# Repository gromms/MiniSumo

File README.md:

# MiniSumo
Repository of mini sumo robot's electronics and programs of "Robotics Project" course.

# Team members
* Gromet Spaal
* Martin Maidla
* Simmo Saan

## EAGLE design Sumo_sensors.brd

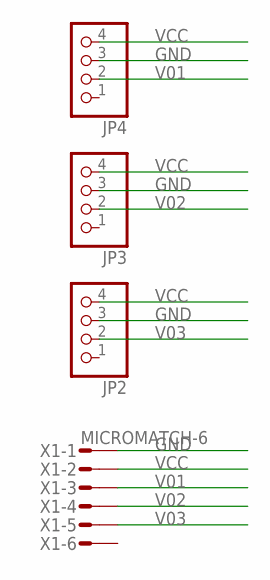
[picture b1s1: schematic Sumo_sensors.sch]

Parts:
JP2, JP3, JP4: PINHD-1X4; 1X04
X1: MICROMATCH-6

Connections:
GND: JP2.3, JP3.3, JP4.3, X1.1
V01: JP4.2, X1.3
V02: JP3.2, X1.4
V03: JP2.2, X1.5
VCC: JP2.4, JP3.4, JP4.4, X1.2

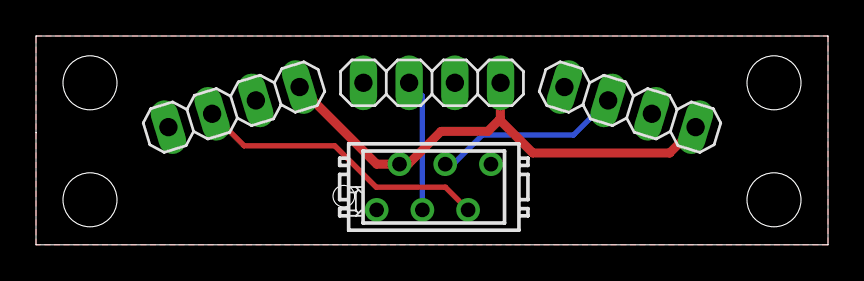
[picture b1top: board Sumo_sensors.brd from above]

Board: 2 copper layers, 44.0 x 11.6 mm, 4 parts (0 on the bottom side), 5 nets.

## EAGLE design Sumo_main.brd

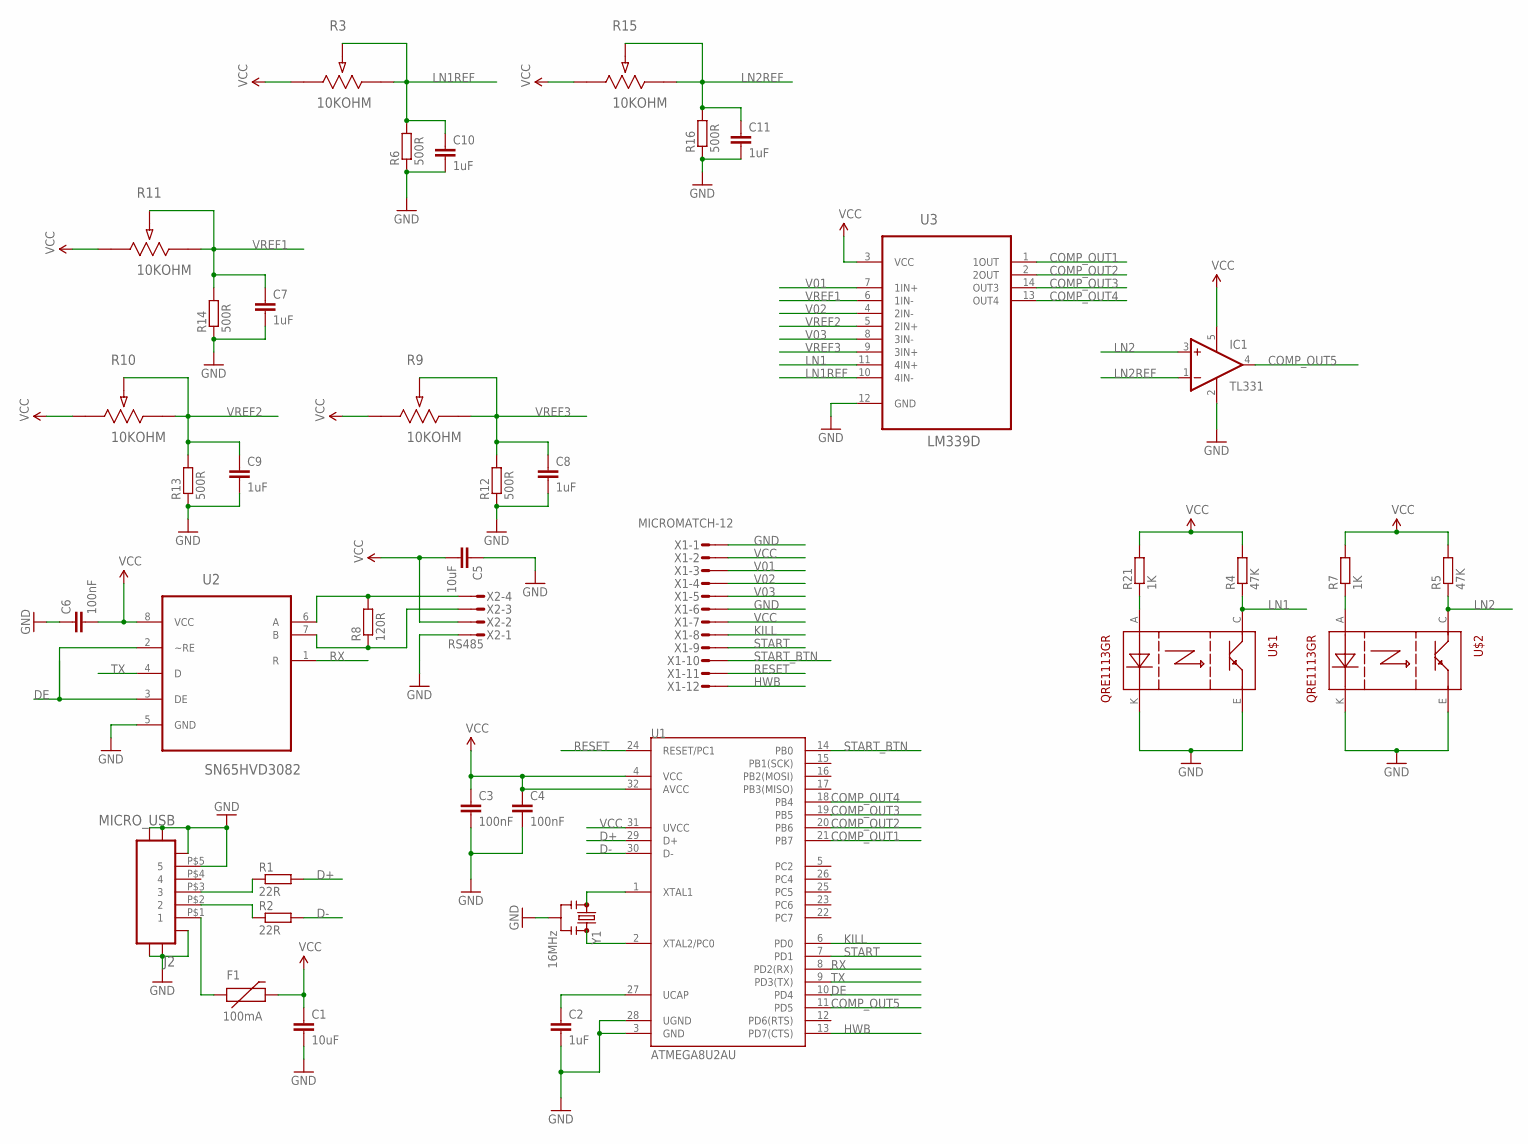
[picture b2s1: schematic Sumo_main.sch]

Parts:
C1, C5: 10uF; 0603-CAP
C2, C7, C8, C9, C10, C11: 1uF; 0603-CAP
C3, C4, C6: 100nF; 0603-CAP
F1: 100mA; PTC-1206
IC1: TL331; DBV-R-PDSO-G5
J2: MICRO_USB; MOLEX_47346-0001
R1, R2: 22R; R0603
R3, R9, R10, R11, R15: 10KOHM; POT_EVM3W
R4, R5: 47K; R0603
R6, R12, R13, R14, R16: 500R; R0603
R7, R21: 1K; R0603
R8: 120R; R0603
U1: ATMEGA8U2AU; TQFP32-08
U2: SN65HVD3082; SOIC127P600X175-8N
U3: LM339D; SOIC127P600X175-14N
U$1, U$2: QRE1113GR; 4LEADSMD
X1: MICROMATCH-12
X2: RS485; MICROMATCH-4
Y1: 16MHz; RESONATOR-SMD_MED

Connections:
COMP_OUT1: U1.21 (PB7), U3.1 (1OUT)
COMP_OUT2: U1.20 (PB6), U3.2 (2OUT)
COMP_OUT3: U1.19 (PB5), U3.14 (OUT3)
COMP_OUT4: U1.18 (PB4), U3.13 (OUT4)
COMP_OUT5: IC1.4 (OUT), U1.11 (PD5)
D+: R1.2, U1.29 (D+)
D-: R2.2, U1.30 (D-)
DE: U1.10 (PD4), U2.2 (~RE), U2.3 (DE)
GND: C1.2, C2.2, C3.2, C4.2, C5.1, C6.1, C7.2, C8.2, C9.2, C10.2, C11.2, IC1.2 (GND), J2.M1, J2.M2, J2.M3, J2.M4, J2.M5, J2.M6, J2.P$5 (5), R6.1, R12.1, R13.1, R14.1, R16.1, U1.3 (GND), U1.28 (UGND), U2.5 (GND), U3.12 (GND), U$1.E, U$1.K, U$2.E, U$2.K, X1.1, X1.6, X2.1, Y1.2
HWB: U1.13 (PD7(CTS)), X1.12
KILL: U1.6 (PD0), X1.8
LN1: R4.1, U3.11 (4IN+), U$1.C
LN1REF: C10.1, R3.2, R3.3, R6.2, U3.10 (4IN-)
LN2: IC1.3 (+IN), R5.1, U$2.C
LN2REF: C11.1, IC1.1 (-IN), R15.2, R15.3, R16.2
unnamed: J2.P$3 (3), R1.1
unnamed: J2.P$2 (2), R2.1
unnamed: F1.1, J2.P$1 (1)
unnamed: R21.1, U$1.A
unnamed: U1.1 (XTAL1), Y1.1
unnamed: U1.2 (XTAL2/PC0), Y1.3
unnamed: C2.1, U1.27 (UCAP)
unnamed: R7.1, U$2.A
unnamed: R8.2, U2.6 (A), X2.4
unnamed: R8.1, U2.7 (B), X2.3
RESET: U1.24 (RESET/PC1), X1.11
RX: U1.8 (PD2(RX)), U2.1 (R)
START: U1.7 (PD1), X1.9
START_BTN: U1.14 (PB0), X1.10
TX: U1.9 (PD3(TX)), U2.4 (D)
V01: U3.7 (1IN+), X1.3
V02: U3.4 (2IN-), X1.4
V03: U3.8 (3IN-), X1.5
VCC: C1.1, C3.1, C4.1, C5.2, C6.2, F1.2, IC1.5 (V+), R3.1, R4.2, R5.2, R7.2, R9.1, R10.1, R11.1, R15.1, R21.2, U1.4 (VCC), U1.31 (UVCC), U1.32 (AVCC), U2.8 (VCC), U3.3 (VCC), X1.2, X1.7, X2.2
VREF1: C7.1, R11.2, R11.3, R14.2, U3.6 (1IN-)
VREF2: C9.1, R10.2, R10.3, R13.2, U3.5 (2IN+)
VREF3: C8.1, R9.2, R9.3, R12.2, U3.9 (3IN+)

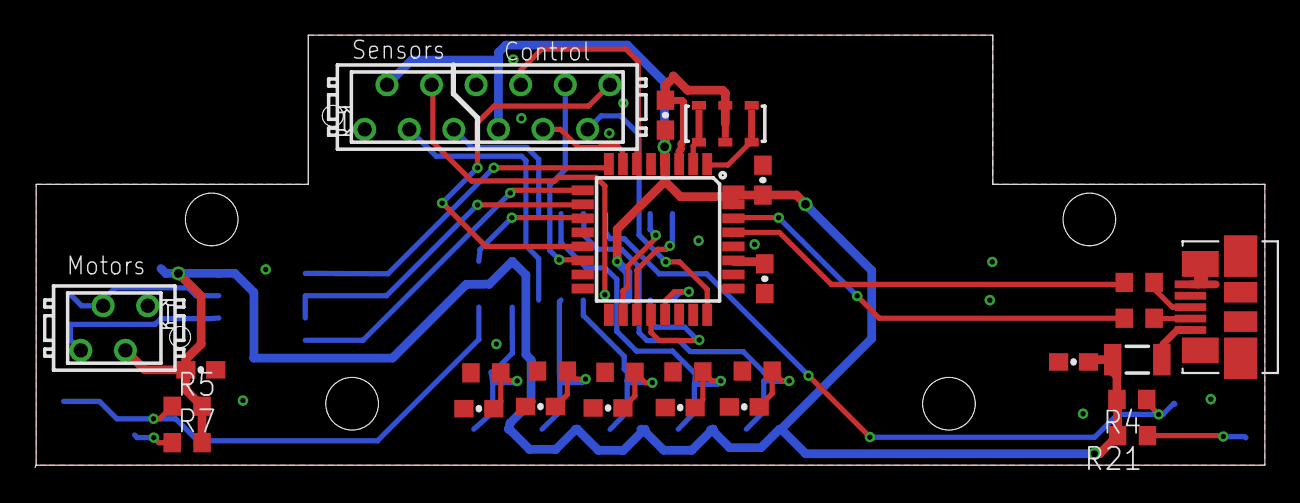
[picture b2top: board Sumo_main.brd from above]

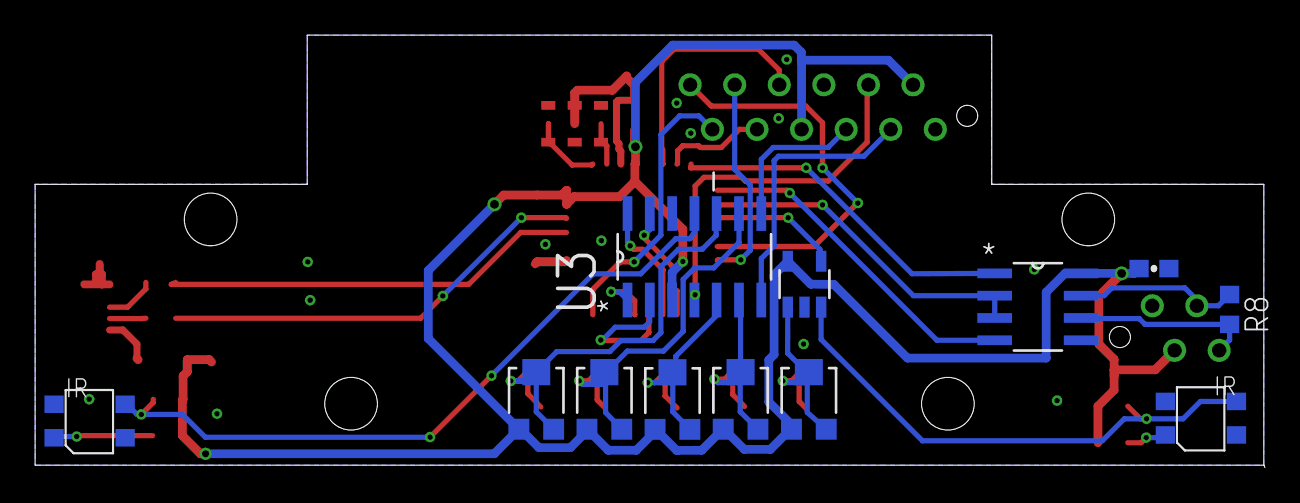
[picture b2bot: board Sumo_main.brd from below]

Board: 2 copper layers, 70.1 x 24.6 mm, 39 parts (12 on the bottom side), 37 nets.

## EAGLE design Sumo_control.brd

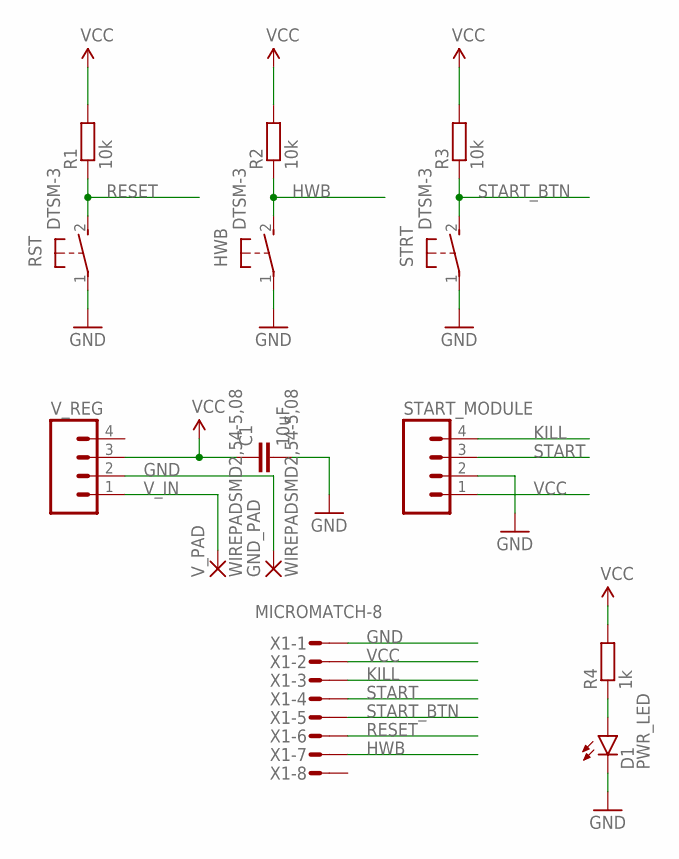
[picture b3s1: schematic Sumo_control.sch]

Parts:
C1: 10uF; 0603-CAP
D1: PWR_LED; LED-0603
GND_PAD: WIREPADSMD2,54-5,08; SMD2,54-5,08
HWB: DTSM-3
R1, R2, R3: 10k; R0603
R4: 1k; R0603
RST: DTSM-3
START_MODULE: M04LONGPADS; 1X04_LONGPADS
STRT: DTSM-3
V_PAD: WIREPADSMD2,54-5,08; SMD2,54-5,08
V_REG: M04LONGPADS; 1X04_LONGPADS
X1: MICROMATCH-8

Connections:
GND: C1.2, D1.C, GND_PAD.1, HWB.1, RST.1, START_MODULE.2, STRT.1, V_REG.2, X1.1
HWB: HWB.2, R2.1, X1.7
KILL: START_MODULE.4, X1.3
unnamed: D1.A, R4.1
RESET: R1.1, RST.2, X1.6
START: START_MODULE.3, X1.4
START_BTN: R3.1, STRT.2, X1.5
VCC: C1.1, R1.2, R2.2, R3.2, R4.2, START_MODULE.1, V_REG.3, X1.2
V_IN: V_PAD.1, V_REG.1

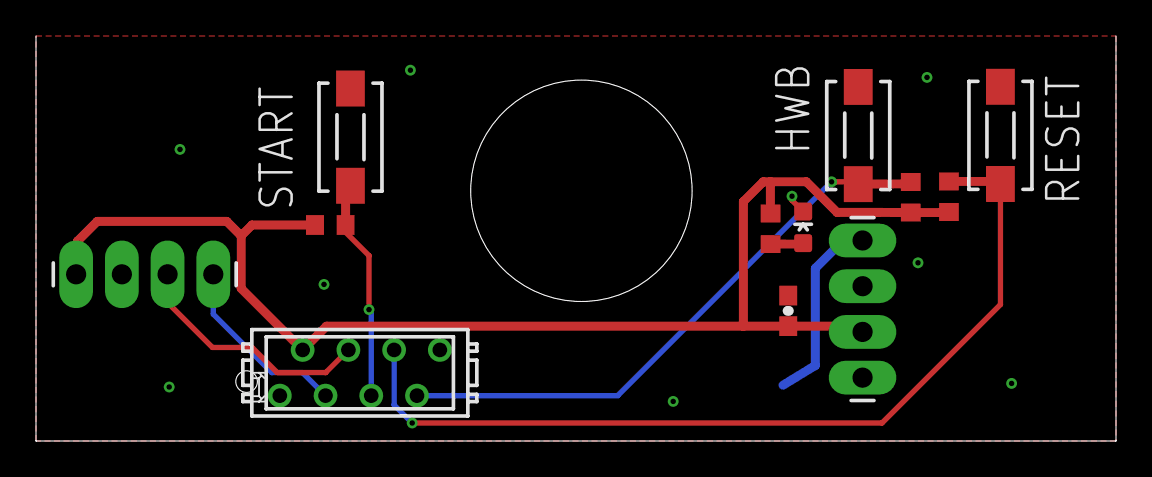
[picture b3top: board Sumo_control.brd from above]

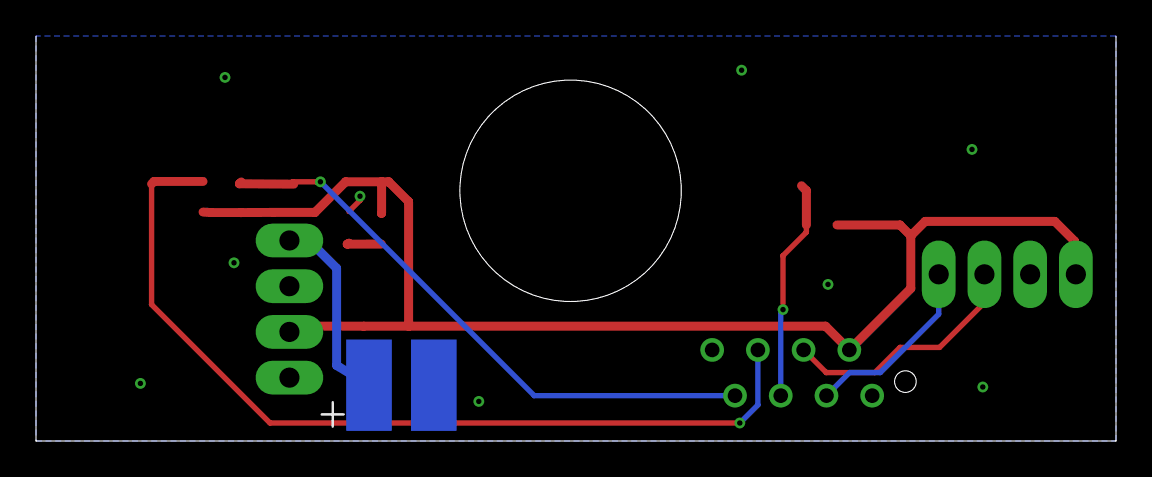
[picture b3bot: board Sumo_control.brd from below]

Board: 2 copper layers, 60.0 x 22.5 mm, 14 parts (2 on the bottom side), 9 nets.

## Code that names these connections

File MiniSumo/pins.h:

#ifndef PINS_H
#define PINS_H

#include <avr/io.h>

// RS485
#define RS485RX PD2
#define RS485TX PD3
#define RS485TXEN PD4

// BTN input
#define START_BTN PB0

// SM inputs
#define KILL PD0
#define START PD1

// DIST inputs
#define DISTL PB5
#define DISTM PB6
#define DISTR PB7
#define DISTS (BIT(DISTL) | BIT(DISTM) | BIT(DISTR))

// LIGHT inputs
#define LIGHTL PB4
#define LIGHTR PD5

// LED
#define LED PD6

#endif

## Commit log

2016-02-04 Added schematic file
2016-02-04 Added RS-485
2016-02-09 Added Non-USB voltage supply.
2016-02-10 Changed RS485 module, added start module and power voltage regulator.
2016-02-10 Changed power switch in schematic for pin headers to connect it with wires later.
2016-02-10 Bug fixes.
2016-02-10 Signal bug fixes.
2016-02-10 Added capacitor to RS-485 chip's VCC and connected RS-485 micromatch VCC capacitor to ground.
2016-02-10 Added ready board and Gerber files.
2016-02-10 Added PNGs of schematic and board, added text to schematic and board and shortened some components' names.
2016-02-16 Version 2 - added comparator for sensor signals, redesigned board to be more compact.
2016-02-16 Re-routed X6 signal and VCC.
2016-02-16 Moved ATMEGA more to center of the board.
2016-02-18 Made the board more compact.
2016-03-03 Added additional button for starting. Changed IR sensors' micromatches to pinheaders.
2016-03-09 Add two IR reflection sensors to detect lines.
2016-03-09 Add PNG pictures of v04 Schematic and Board.
2016-03-31 Add MainMod testing code
2016-03-31 Create .gitignore for C, CodeBlocks, AVR
2016-03-31 Move MainMod testing code to separate directory
2016-04-04 Add line sensor to schematic.
2016-04-04 Start arranging new board.
2016-04-04 Remove unnecessary components that are moved to other board.
2016-04-04 Board redesign. TODO: Connect HWB
2016-04-04 Add control board schematic and board
2016-04-05 Finish and fix errors of Main's schematic and board
2016-04-05 Wire one unwired signal
2016-04-05 remove unnecessary files
2016-04-05 Remove old Gerber folder and files
2016-04-05 Adjust control board to meet right EDC requirements
2016-04-12 Add mounting holes to board and re-route some wires to get rid of some vias.
2016-04-12 Adjust GND plate to actual board shape
2016-04-12 Adjust blocks' placements
2016-04-12 Add isolation to polygon
2016-04-12 Mark correct PCB shape
2016-04-12 Replace power pads with bigger ones
2016-04-12 Add SeeedStudio DRU
2016-04-14 Add STEP files of component-less main board
2016-04-14 Final modifications before test order
2016-05-06 Create code for atmega8u2
2016-05-06 Clean up imported code
2016-05-06 Fix CodeBlocks project file
2016-05-12 Reorder DIST pins
2016-05-13 Tested dual motor communication and all distance sensors
2016-05-24 Swap light sensor left and right to match reality
2016-05-24 Reverse from black line
2016-05-25 Add LED and START_BTN interrupt
2016-05-26 Replace START_BTN interrupt with polling
2016-05-26 Update main board and schematic
2016-05-26 Add sensor board and schematic
2016-05-26 Remove button-sensor code
2016-05-26 Invert light sensor values for white border
2016-05-26 Implement basic slow sumo logic
2016-05-26 Fix distance sensor order
2016-05-26 Working middle distance logic
2016-05-26 Fix left/right distance sensor side
2016-05-26 Fix both attack turns being same, increase speeds
2016-05-27 Replace single wheel turn reversing with single wheel forwarding
2016-06-01 Reduce speeds for unsuitable battery mass placement
2016-06-01 Remove unused variable
2016-06-01 Create function for driving motors
2016-06-01 Change positive speeds to be forward
2016-06-01 Fix drive command
2016-06-02 Reduce speeds even further, shorten reaction delay
2016-06-02 Add delay between motor commands to ensure both motors receive correctly
2016-06-02 Make turning more accurate

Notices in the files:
parts and their libraries:
SparkFun-Connectors: Licensing: Creative Commons ShareAlike 4.0 International - https://creativecommons.org/licenses/by-sa/4.0
